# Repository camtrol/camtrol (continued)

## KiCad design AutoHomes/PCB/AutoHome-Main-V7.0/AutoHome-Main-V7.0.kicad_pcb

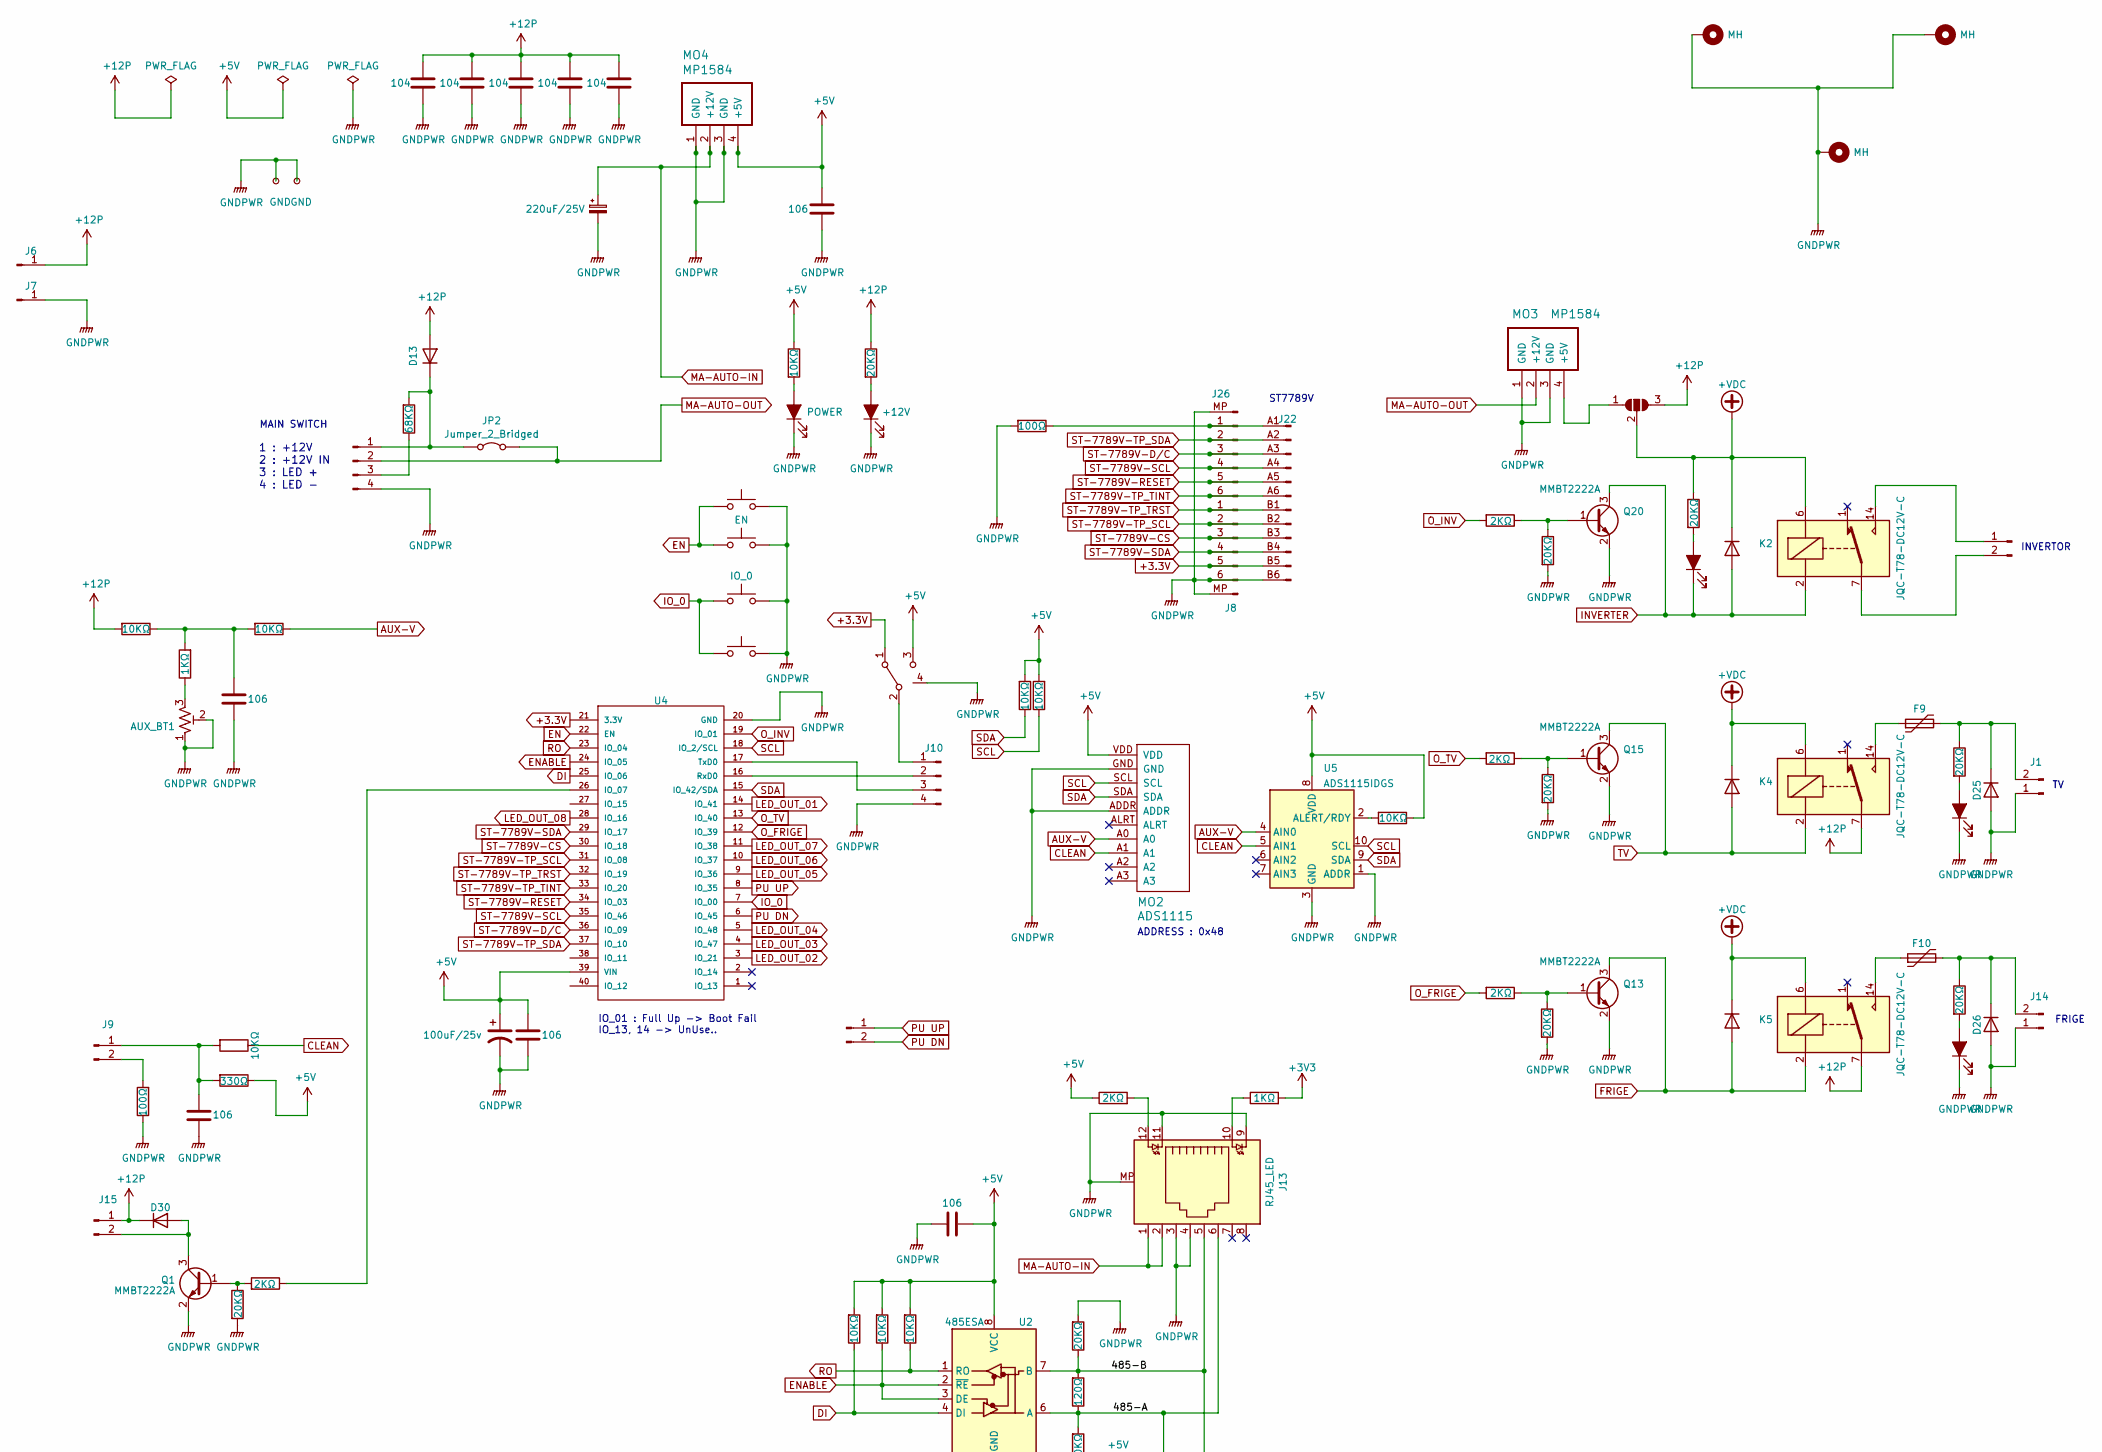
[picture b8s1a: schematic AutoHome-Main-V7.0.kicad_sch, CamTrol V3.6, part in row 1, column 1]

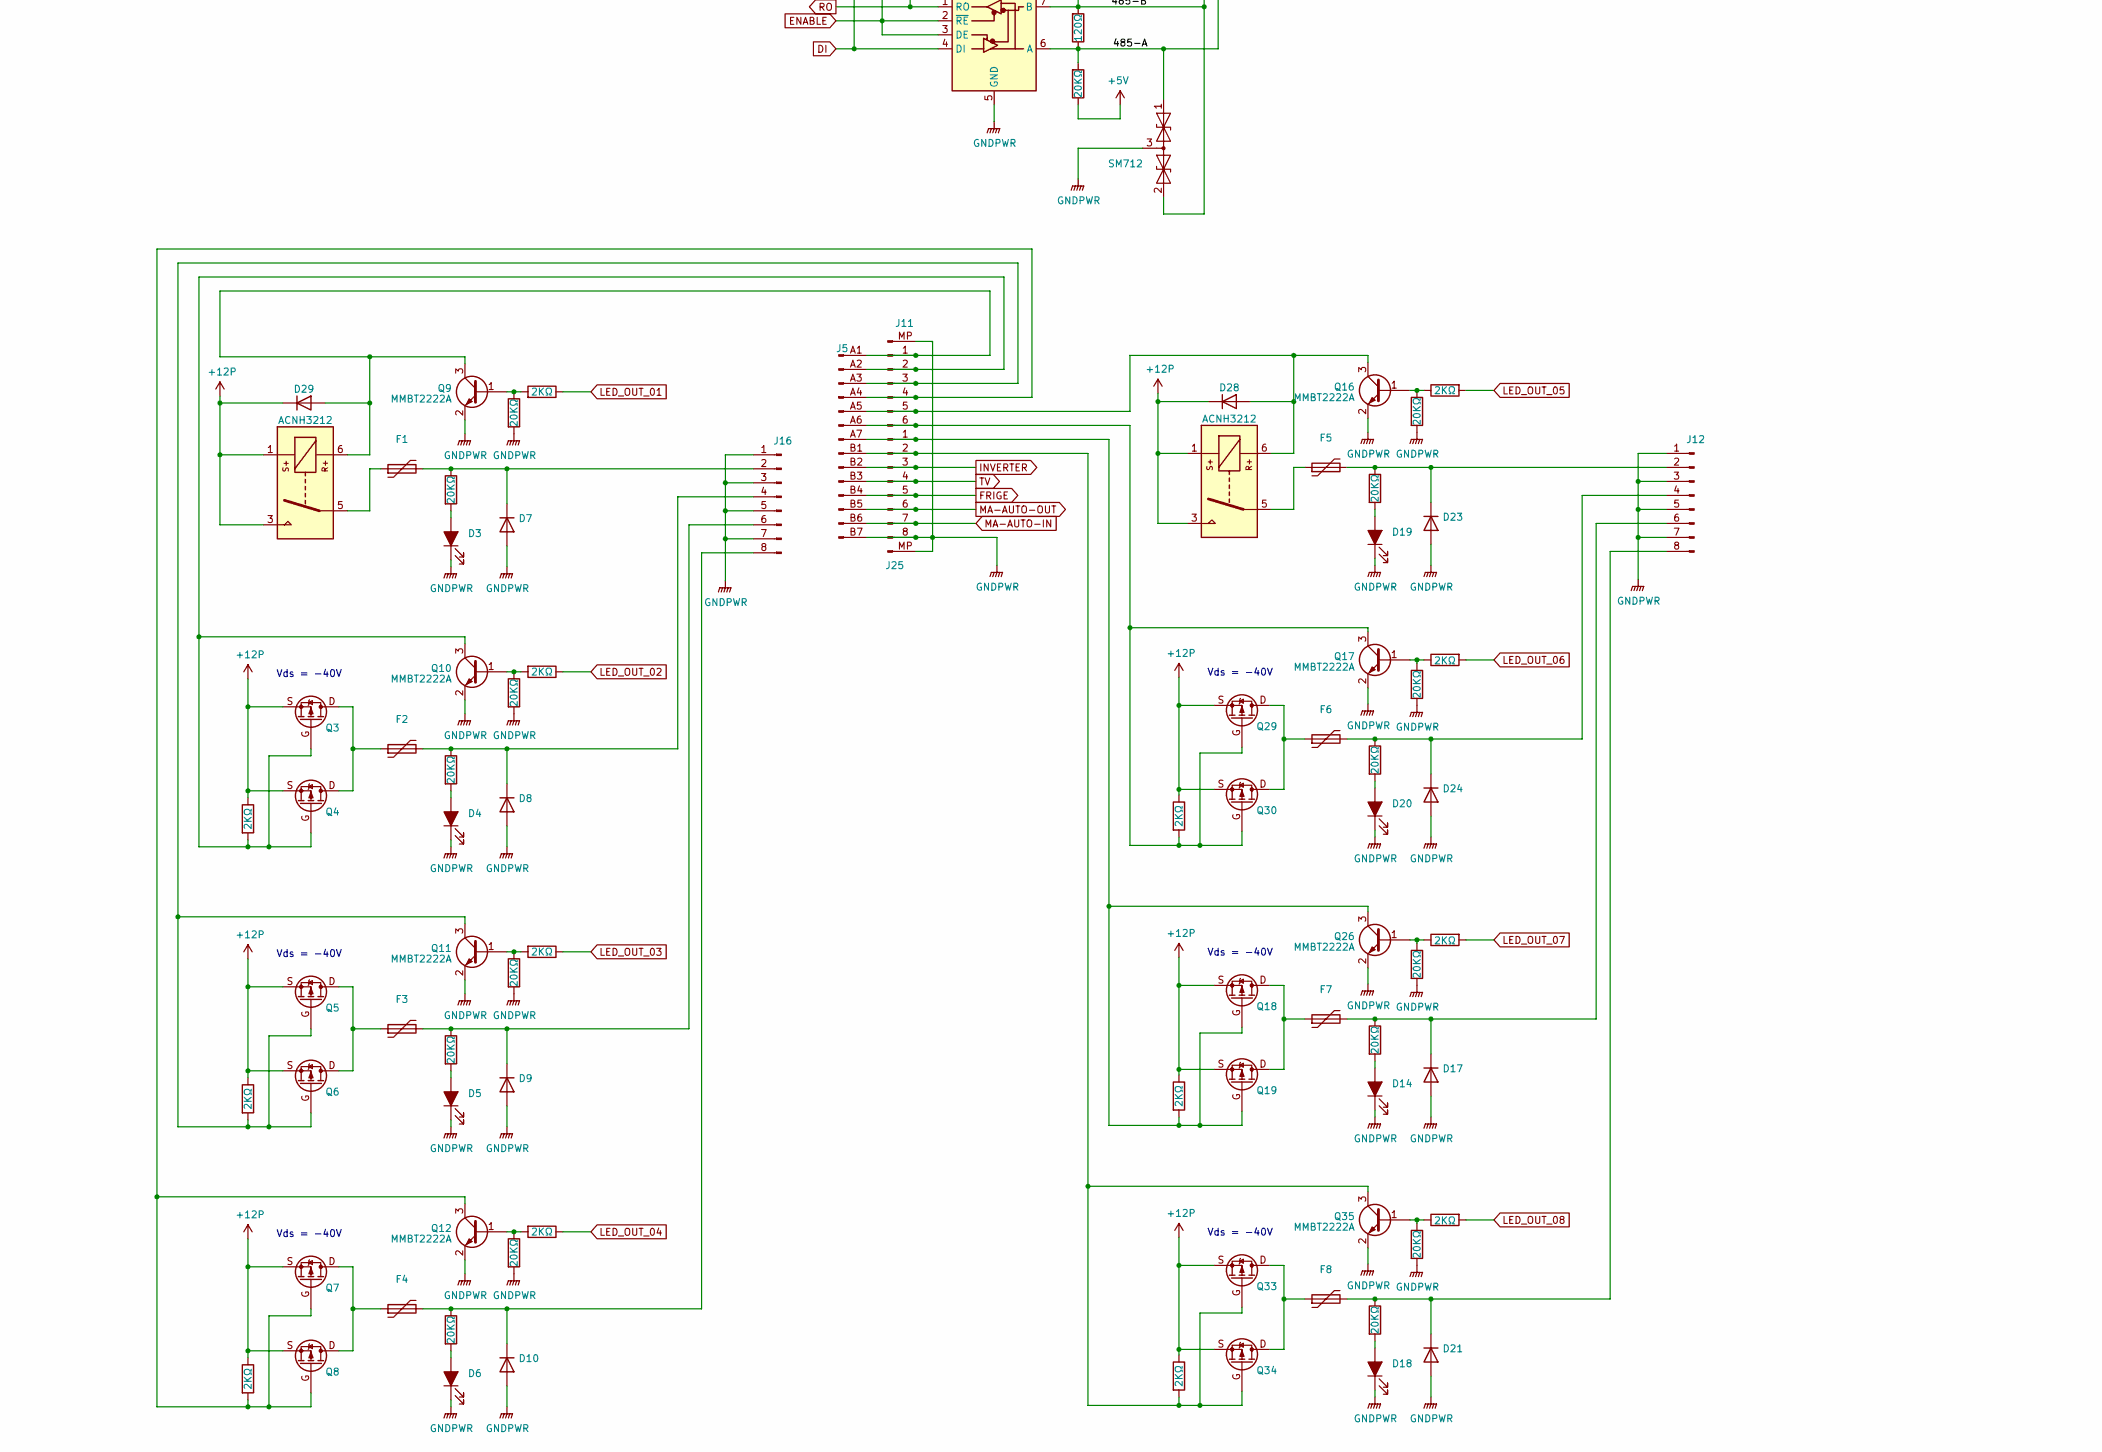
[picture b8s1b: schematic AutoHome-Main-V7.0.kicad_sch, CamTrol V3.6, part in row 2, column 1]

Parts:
AUX_BT1: B3296Y-2KΩ; Potentiometer_Bourns_3296Y_Vertical
C2: 100uF/25v; CP_Elec_6.3x5.3
C3, C4, C6, C12, C20: 106; C_0805_HandSoldering
C5: 220uF/25V; CP_Radial_D8.0mm_P2.50mm
C7, C9, C10, C11, C13: 104; C_0805_HandSoldering
D1, D3, D4, D5, D6, D14, D16, D18, D19, D20, D22: RED LED; LED_0805
D2, D12, D15, D28, D29: 4007; D_SOD-123
D7, D8, D9, D10, D17, D21, D23, D24, D25, D26, D30: 4007; D_SMA
D11: POWER; LED_0805
D13: SS34; D_SMA
D27: +12V; LED_0805
D31: SM712; SOT-23
F1, F2, F3, F4, F5, F6, F7, F8, F9, F10: FRG500-16F; FUSE-PIN-Holder-Mini
H1, H2, H7: MH; MountingHole_3.2mm_M3-pcb
J1, J14: Conn_01x02_Pin; KF7.62-2P
J4, J24: ECH381V-2P; PhoenixContact_MC_1,5_2-G-3.81_1x02_P3.81mm_Horizontal
J5: Conn_01x12_Male; IDC-Header_2x07_P2.54mm_Vertical
J6, J7: BR-120
J8, J11, J26: Conn_01x06_Pin; JST_GH_SM06B-GHS-TB_1x06-1MP_P1.25mm_Horizontal
J9, J15: ECH381V-2P; PhoenixContact_MCV_1,5_2-G-3.81_1x02_P3.81mm_Vertical
J10: 5267-04P; Molex_SPOX_5267-04A_1x04_P2.50mm_Vertical
J12, J16: Conn_01x14_Pin; KF7.62-8P
J13: RJ45_LED; RJ45_LED_SMD
J17: Conn_01x04_Pin; PhoenixContact_MCV_1,5_4-G-3.81_1x04_P3.81mm_Vertical
J22: Conn_01x12_Male; IDC-Header_2x06_P2.54mm_Vertical
J25: Conn_01x08_Pin; JST_GH_SM08B-GHS-TB_1x08-1MP_P1.25mm_Horizontal
JP1: SolderJumper_3_Open; SolderJumper-3_P1.3mm_Open_RoundedPad1.0x1.5mm
JP2: Jumper_2_Bridged; SolderJumper-2_P1.3mm_Bridged_RoundedPad1.0x1.5mm
K1, K3: ACNH3212
K2, K4, K5: JQC-T78-DC12V-C
MO2: ADS1115
MO3: MP1584; MP1584-SMD
MO4: MP1584; TZT-SMD
Q1, Q9, Q10, Q11, Q12, Q13, Q15, Q16, Q17, Q20, Q26, Q35: MMBT2222A; SOT-23
Q3, Q4, Q5, Q6, Q7, Q8, Q18, Q19, Q29, Q30, Q33, Q34: AOD4185; AOD1485
R1, R3, R6, R10, R19, R21, R23, R25, R34, R37, R38, R42, R43, R44, R45, R46, R47, R48, R49, R50, R53, R54, R55, R56, R57, R58: 20KΩ; R_0805_HandSoldering
R2, R22: 100Ω; R_0805_HandSoldering
R4: 68KΩ; R_0805_HandSoldering
R5, R7, R8, R9, R11, R13, R14, R15, R16, R20, R24, R26, R28, R29, R30, R31, R51, R52, R66: 2KΩ; R_0805_HandSoldering
R12, R17, R18, R27, R32, R33, R35, R41, R74, R79: 10KΩ; R_0805_HandSoldering
R36: 120Ω; R_0805_HandSoldering
R39: 330Ω; R_0805_HandSoldering
R40, R77: 1KΩ; R_0805_HandSoldering
SW1: EN; SW_SPST_CK_RS282G05A3
SW2: IO_0; SW_SPST_CK_RS282G05A3
SW3: NW3-SK-02
SW5, SW6: SW_Push; TS-3404
TP1, TP2: GND; Test_Point_Keystone_5000-5004_Miniature
U2: 485ESA; MAX485
U4: ESP32-S3
U5: ADS1115IDGS; TSSOP-10_3x3mm_P0.5mm

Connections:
+3.3V: J8.5, J22.B5 (Pin_11), SW3.1 (A), U4.21 (3.3V)
+3V3: R40.2
+5V: C2.1, C3.1, C4.1, C12.1, MO2.VDD, MO4.4 (+5V), R12.2, R17.2, R18.2, R24.1, R27.2, R33.2, R35.1, R37.1, R39.1, R41.1, SW3.3 (C), U2.8 (VCC), U4.39 (VIN), U5.8 (VDD); also elsewhere on the board
+12P: C7.1, C9.1, C10.1, C11.1, C13.1, D13.1 (A), D28.2 (K), D29.2 (K), D30.2 (K), J6.1, J15.1, JP1.3 (B), K1.1, K1.3, K3.1, K3.3, K4.7, K5.7, Q3.S (Source), Q4.S (Source), Q5.S (Source), Q6.S (Source), Q7.S (Source), Q8.S (Source), Q18.S (Source), Q19.S (Source), Q29.S (Source), Q30.S (Source), Q33.S (Source), Q34.S (Source), R1.1, R5.1, R9.1, R14.1, R15.1, R16.1, R66.1, R74.2
+VDC: D2.2 (K), D12.2 (K), D15.2 (K), JP1.2 (C), K2.6, K4.6, K5.6, R55.1
/485-A: D31.1 (A1), J13.6, R36.1, R37.2, U2.6 (A)
/485-B: D31.2 (A2), J13.5, R34.1, R36.2, U2.7 (B)
AUX-V: MO2.A0, R79.1, U5.4 (AIN0); also elsewhere on the board
CLEAN: MO2.A1, R32.1, U5.5 (AIN1); also elsewhere on the board
DI: R18.1, U2.4 (DI), U4.25 (IO_06)
EN: SW1.1, SW5.1, U4.22 (EN)
ENABLE: R27.1, U2.2 (~RE), U2.3 (DE), U4.24 (IO_05)
FRIGE: D2.1 (A), J5.B4 (Pin_8), J25.5, K5.2, Q13.3 (C)
GNDPWR: AUX_BT1.1, AUX_BT1.2, C2.2, C3.2, C4.2, C5.2, C6.2, C7.2, C9.2, C10.2, C11.2, C12.2, C13.2, C20.2, D3.1 (K), D4.1 (K), D5.1 (K), D6.1 (K), D7.1 (A), D8.1 (A), D9.1 (A), D10.1 (A), D11.1 (K), D14.1 (K), D16.1 (K), D17.1 (A), D18.1 (K), D19.1 (K), D20.1 (K), D21.1 (A), D22.1 (K), D23.1 (A), D24.1 (A), D25.1 (A), D26.1 (A), D27.1 (K), D31.3 (common), H1.1, H2.1, H7.1, J1.1, J5.B7 (Pin_14), J7.1, J8.6, J8.MP (Pin_7), J10.4, J11.MP (Pin_1), J12.1, J12.3, J12.5, J12.7, J13.3, J13.4, J13.9, J13.11, J13.MP, J14.1, J16.1, J16.3, J16.5, J16.7, J17.4, J22.B6 (Pin_12), J25.8, J25.MP (Pin_9), J26.MP (Pin_1), MO2.1, MO2.3, MO2.ADDR, MO2.GND, MO3.1 (GND), MO3.3 (GND), MO4.1 (GND), MO4.3 (GND), Q1.2 (E), Q9.2 (E), Q10.2 (E), Q11.2 (E), Q12.2 (E), Q13.2 (E), Q15.2 (E), Q16.2 (E), Q17.2 (E), Q20.2 (E), Q26.2 (E), Q35.2 (E), R2.2, R3.2, R22.1, R34.2, R38.2, R42.2, R43.2, R45.2, R47.2, R48.2, R49.2, R50.2, R53.2, R54.2, R58.2, SW1.2, SW2.2, SW3.4 (C), SW5.2, SW6.2, TP1.1, TP2.1, U2.5 (GND), U4.20 (GND), U5.1 (ADDR), U5.3 (GND); also elsewhere on the board
INVERTER: D1.1 (K), D15.1 (A), J5.B2 (Pin_4), J25.3, K2.2, Q20.3 (C)
IO_0: SW2.1, SW6.1, U4.7 (IO_00)
LED_OUT_01: R28.1, U4.14 (IO_41)
LED_OUT_02: R29.1, U4.3 (IO_21)
LED_OUT_03: R30.1, U4.4 (IO_47)
LED_OUT_04: R31.1, U4.5 (IO_48)
LED_OUT_05: R51.2, U4.9 (IO_36)
LED_OUT_06: R52.2, U4.10 (IO_37)
LED_OUT_07: R8.2, U4.11 (IO_38)
LED_OUT_08: R11.2, U4.28 (IO_16)
MA-AUTO-IN: C5.1, J5.B6 (Pin_12), J13.1, J13.2, J25.7, MO4.2 (+12V)
MA-AUTO-OUT: J5.B5 (Pin_10), J17.2, J25.6, JP2.2 (B), MO3.2 (+12V)
unnamed: AUX_BT1.3, R77.1
unnamed: C20.1, R74.1, R77.2, R79.2
unnamed: D1.2 (A), R55.2
unnamed: D3.2 (A), R19.2
unnamed: D4.2 (A), R21.2
unnamed: D5.2 (A), R23.2
unnamed: D6.2 (A), R25.2
unnamed: D7.2 (K), F1.2, J16.2, R19.1
unnamed: D8.2 (K), F2.2, J16.4, R21.1
unnamed: D9.2 (K), F3.2, J16.6, R23.1
unnamed: D10.2 (K), F4.2, J16.8, R25.1
unnamed: D11.2 (A), R35.2
unnamed: D13.2 (K), J17.1, JP2.1 (A), R4.2
unnamed: D14.2 (A), R6.2
unnamed: D16.2 (A), R56.2
unnamed: D17.2 (K), F7.2, J12.6, R6.1
unnamed: D18.2 (A), R10.2
unnamed: D19.2 (A), R44.2
unnamed: D20.2 (A), R46.2
unnamed: D21.2 (K), F8.2, J12.8, R10.1
unnamed: D22.2 (A), R57.2
unnamed: D23.2 (K), F5.2, J12.2, R44.1
unnamed: D24.2 (K), F6.2, J12.4, R46.1
unnamed: D25.2 (K), F9.2, J1.2, R56.1
unnamed: D26.2 (K), F10.2, J14.2, R57.1
unnamed: D27.2 (A), R1.2
unnamed: D28.1 (A), J5.A5 (Pin_9), J11.5 (Pin_6), K3.6, Q16.3 (C)
unnamed: D29.1 (A), J5.A1 (Pin_1), J11.1 (Pin_2), K1.6, Q9.3 (C)
unnamed: D30.1 (A), J15.2, Q1.3 (C)
unnamed: F1.1, K1.5
unnamed: F5.1, K3.5
unnamed: F9.1, K4.14
unnamed: F10.1, K5.14
unnamed: J4.1, K2.14
unnamed: J4.2, K2.7
unnamed: C6.1, J9.1, R32.2, R39.2
unnamed: J9.2, R22.2
unnamed: J10.1, SW3.2 (B)
unnamed: J10.2, U4.16 (RxD0)
unnamed: J10.3, U4.17 (TxD0)
unnamed: J5.A2 (Pin_3), J11.2 (Pin_3), Q3.G (Gate), Q4.G (Gate), Q10.3 (C), R14.2
unnamed: J5.A3 (Pin_5), J11.3 (Pin_4), Q5.G (Gate), Q6.G (Gate), Q11.3 (C), R15.2
unnamed: J5.A4 (Pin_7), J11.4 (Pin_5), Q7.G (Gate), Q8.G (Gate), Q12.3 (C), R16.2
unnamed: J5.A6 (Pin_11), J11.6 (Pin_7), Q17.3 (C), Q29.G (Gate), Q30.G (Gate), R66.2
unnamed: J13.10, R40.1
unnamed: J13.12, R24.2
unnamed: J17.3, R4.1
unnamed: J22.A1 (Pin_1), J26.1 (Pin_2), R2.1
unnamed: J5.A7 (Pin_13), J25.1, Q18.G (Gate), Q19.G (Gate), Q26.3 (C), R5.2
unnamed: J5.B1 (Pin_2), J25.2, Q33.G (Gate), Q34.G (Gate), Q35.3 (C), R9.2
unnamed: JP1.1 (A), MO3.4 (+5V)
unnamed: Q1.1 (B), R3.1, R13.2
unnamed: F2.1, Q3.D (Drain), Q4.D (Drain)
unnamed: F3.1, Q5.D (Drain), Q6.D (Drain)
unnamed: F4.1, Q7.D (Drain), Q8.D (Drain)
unnamed: Q9.1 (B), R28.2, R48.1
unnamed: Q10.1 (B), R29.2, R49.1
unnamed: Q11.1 (B), R30.2, R50.1
unnamed: Q12.1 (B), R31.2, R53.1
unnamed: Q13.1 (B), R26.1, R42.1
unnamed: Q15.1 (B), R7.1, R54.1
unnamed: Q16.1 (B), R47.1, R51.1
unnamed: Q17.1 (B), R45.1, R52.1
unnamed: F7.1, Q18.D (Drain), Q19.D (Drain)
unnamed: Q20.1 (B), R20.1, R58.1
unnamed: Q26.1 (B), R8.1, R43.1
unnamed: F6.1, Q29.D (Drain), Q30.D (Drain)
unnamed: F8.1, Q33.D (Drain), Q34.D (Drain)
unnamed: Q35.1 (B), R11.1, R38.1
unnamed: R13.1, U4.26 (IO_07)
unnamed: R41.2, U5.2 (ALERT/RDY)
O_FRIGE: R26.2, U4.12 (IO_39)
O_INV: R20.2, U4.19 (IO_01)
O_TV: R7.2, U4.13 (IO_40)
PU DN: J24.2, U4.6 (IO_45)
PU UP: J24.1, U4.8 (IO_35)
RO: R33.1, U2.1 (RO), U4.23 (IO_04)
SCL: MO2.SCL, R12.1, U4.18 (IO_2/SCL), U5.10 (SCL); also elsewhere on the board
SDA: MO2.SDA, R17.1, U4.15 (IO_42/SDA), U5.9 (SDA); also elsewhere on the board
ST-7789V-CS: J8.3, J22.B3 (Pin_9), U4.30 (IO_18)
ST-7789V-D/C: J22.A3 (Pin_3), J26.3 (Pin_4), U4.36 (IO_09)
ST-7789V-RESET: J22.A5 (Pin_5), J26.5 (Pin_6), U4.34 (IO_03)
ST-7789V-SCL: J22.A4 (Pin_4), J26.4 (Pin_5), U4.35 (IO_46)
ST-7789V-SDA: J8.4, J22.B4 (Pin_10), U4.29 (IO_17)
ST-7789V-TP_SCL: J8.2, J22.B2 (Pin_8), U4.31 (IO_08)
ST-7789V-TP_SDA: J22.A2 (Pin_2), J26.2 (Pin_3), U4.37 (IO_10)
ST-7789V-TP_TINT: J22.A6 (Pin_6), J26.6 (Pin_7), U4.33 (IO_20)
ST-7789V-TP_TRST: J8.1, J22.B1 (Pin_7), U4.32 (IO_19)
TV: D12.1 (A), J5.B3 (Pin_6), J25.4, K4.2, Q15.3 (C)

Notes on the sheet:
Vds = -40V
ST7789V
FRIGE
INVERTOR
ADDRESS : 0x48
IO_01 : Full Up -> Boot Fail IO_13, 14 -> UnUse..
1 : +12V 2 : +12V IN 3 : LED + 4 : LED -
MAIN SWITCH

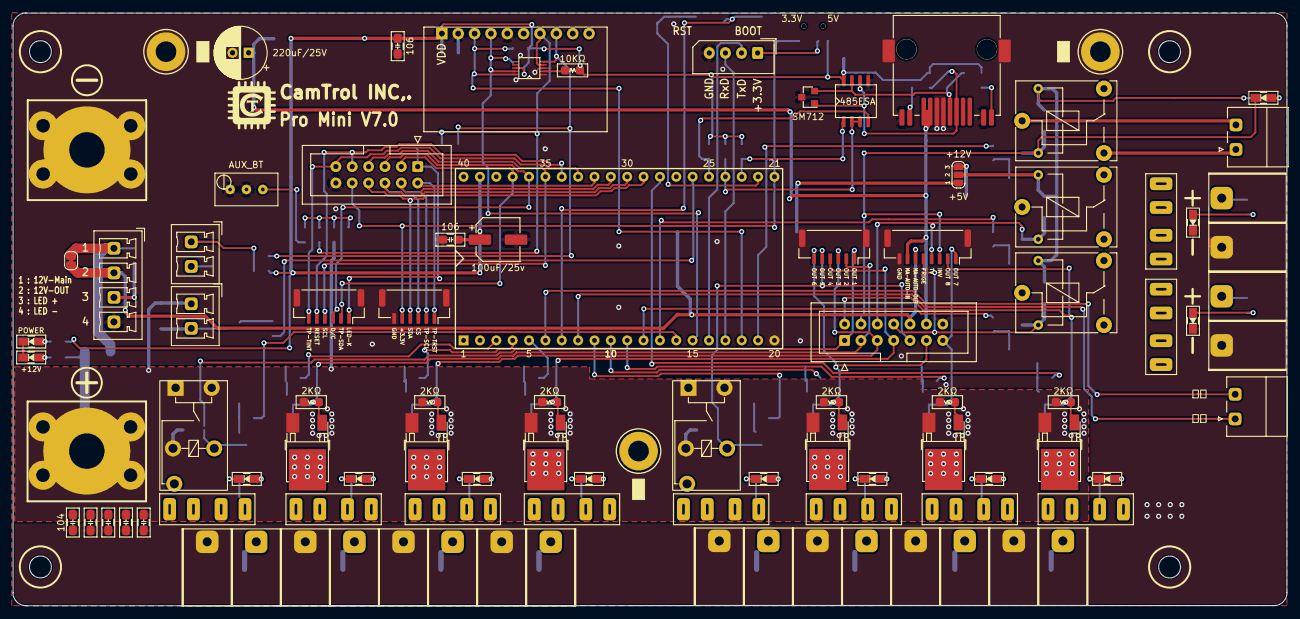
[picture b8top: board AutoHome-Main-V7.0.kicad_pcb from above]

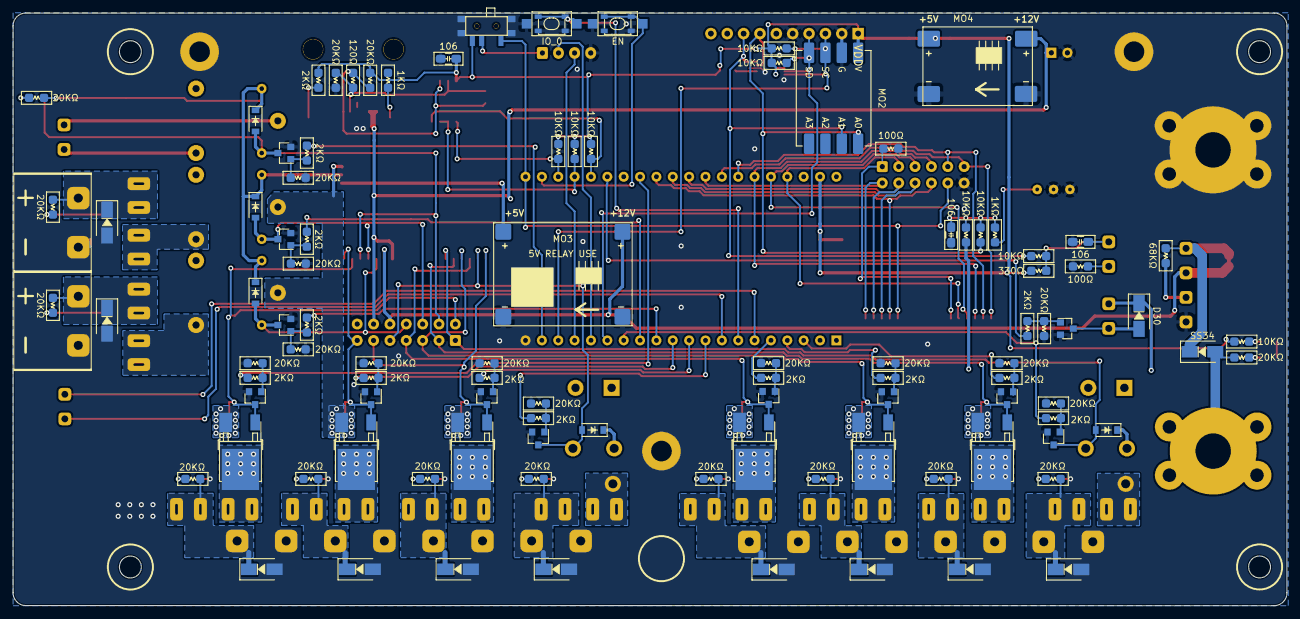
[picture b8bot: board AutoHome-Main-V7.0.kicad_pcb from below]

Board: 2 copper layers, 197.8 x 92.0 mm, 181 parts (101 on the bottom side), 114 nets.

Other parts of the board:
MO2#2: ADS1115_SMD

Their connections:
+5V: MO2#2.VCC; also elsewhere on the board
AUX-V: MO2#2.A0; also elsewhere on the board
CLEAN: MO2#2.A1; also elsewhere on the board
GNDPWR: MO2#2.GND; also elsewhere on the board
SCL: MO2#2.SCL; also elsewhere on the board
SDA: MO2#2.SDA; also elsewhere on the board

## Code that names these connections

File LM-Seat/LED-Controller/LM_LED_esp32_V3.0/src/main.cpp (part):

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#define LED3 48
#define LED4 45
#define LED5 41
// #define FLOOR 41

#define MAIN_VOLT 17

#define LiPo 8
// #define POWER 17
#define SWITCH 19
#define DOOR 20

#define DOOR_TYPE 12

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#define NEO_PIN_1 15
#define NEO_PIN_2 16

#define NEO_1_RGB 9  // NEO 1 RGB Switch
#define NEO_2_RGB 10 // NEO 2 RGB Switch

#define SWITCH_LED 1
#define DOOR_LED 39
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void setup() {

  pinMode(ENABLE, OUTPUT);
  pinMode(LiPo, INPUT_PULLDOWN);
  pinMode(DOOR, INPUT_PULLUP);
  pinMode(NEO_1_RGB, INPUT_PULLUP);
  pinMode(NEO_2_RGB, INPUT_PULLUP);

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
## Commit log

2025-03-09 first commi
2025-03-09 readme.md 추가
2025-03-09 LM con v3.2 up
2025-03-09 2025-03-09-20:42 commit
2025-03-09 readme.md 수정
